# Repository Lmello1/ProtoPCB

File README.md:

# ProtoPCB

Business card PCB and pocket Attiny3227 and LED matrix playground. Powered by a CR2032 battery

## Description

A business card PCB based on the ATTINY3227 chipset. Using 4 74HC595D shift registers to drive a 256 LED matrix. With a standard UDPI interface and 3 input buttons the possibilities are endless.
The current code includes various games and demo programs. Please feel free to make your own and share!

NOTE: Shift register U3 is reversed for easier routing.

## Current programs
* Snake

## Coming soon
* Pong
* Tic Tac Toe
* Tetris

## LED matrix info
```
                 led matrix data flow
attiny3227
V
\_________>_______________________>______________________
         U1                      U2                      \
 ____________________    ____________________             |
/                    \  /                    \            |
X  X  X  X  X  X  X  X  X  X  X  X  X  X  X  X \          |
X  X  X  X  X  X  X  X  X  X  X  X  X  X  X  X |          |
X  X  X  X  X  X  X  X  X  X  X  X  X  X  X  X |          |
X  X  X  X  X  X  X  X  X  X  X  X  X  X  X  X |---- U3---V--(REVERSED)
X  X  X  X  X  X  X  X  X  X  X  X  X  X  X  X |          |
X  X  X  X  X  X  X  X  X  X  X  X  X  X  X  X |          |
X  X  X  X  X  X  X  X  X  X  X  X  X  X  X  X |          |
X  X  X  X  X  X  X  X  X  X  X  X  X  X  X  X /          |
X  X  X  X  X  X  X  X  X  X  X  X  X  X  X  X \          |
X  X  X  X  X  X  X  X  X  X  X  X  X  X  X  X |          |
X  X  X  X  X  X  X  X  X  X  X  X  X  X  X  X |          |
X  X  X  X  X  X  X  X  X  X  X  X  X  X  X  X |---- U4   V
X  X  X  X  X  X  X  X  X  X  X  X  X  X  X  X |          |
X  X  X  X  X  X  X  X  X  X  X  X  X  X  X  X |          |
X  X  X  X  X  X  X  X  X  X  X  X  X  X  X  X |          |
X  X  X  X  X  X  X  X  X  X  X  X  X  X  X  X /          *
```

## PCB Revision History
* Rev 1.0 - 1st working version (Do not recreate-one shorted track) NOTE: Removed from github

* Rev 2.0 - Vertical PCB format and visual improvements. Changed foorptints for shift registers

* Rev 3.0 - CR2032 battery holder added for the back, Track routing improvements

## Creators

Landon Mello
[@Landon_Mello](https://twitter.com/Landon_Mello_)

Ben Liebmann

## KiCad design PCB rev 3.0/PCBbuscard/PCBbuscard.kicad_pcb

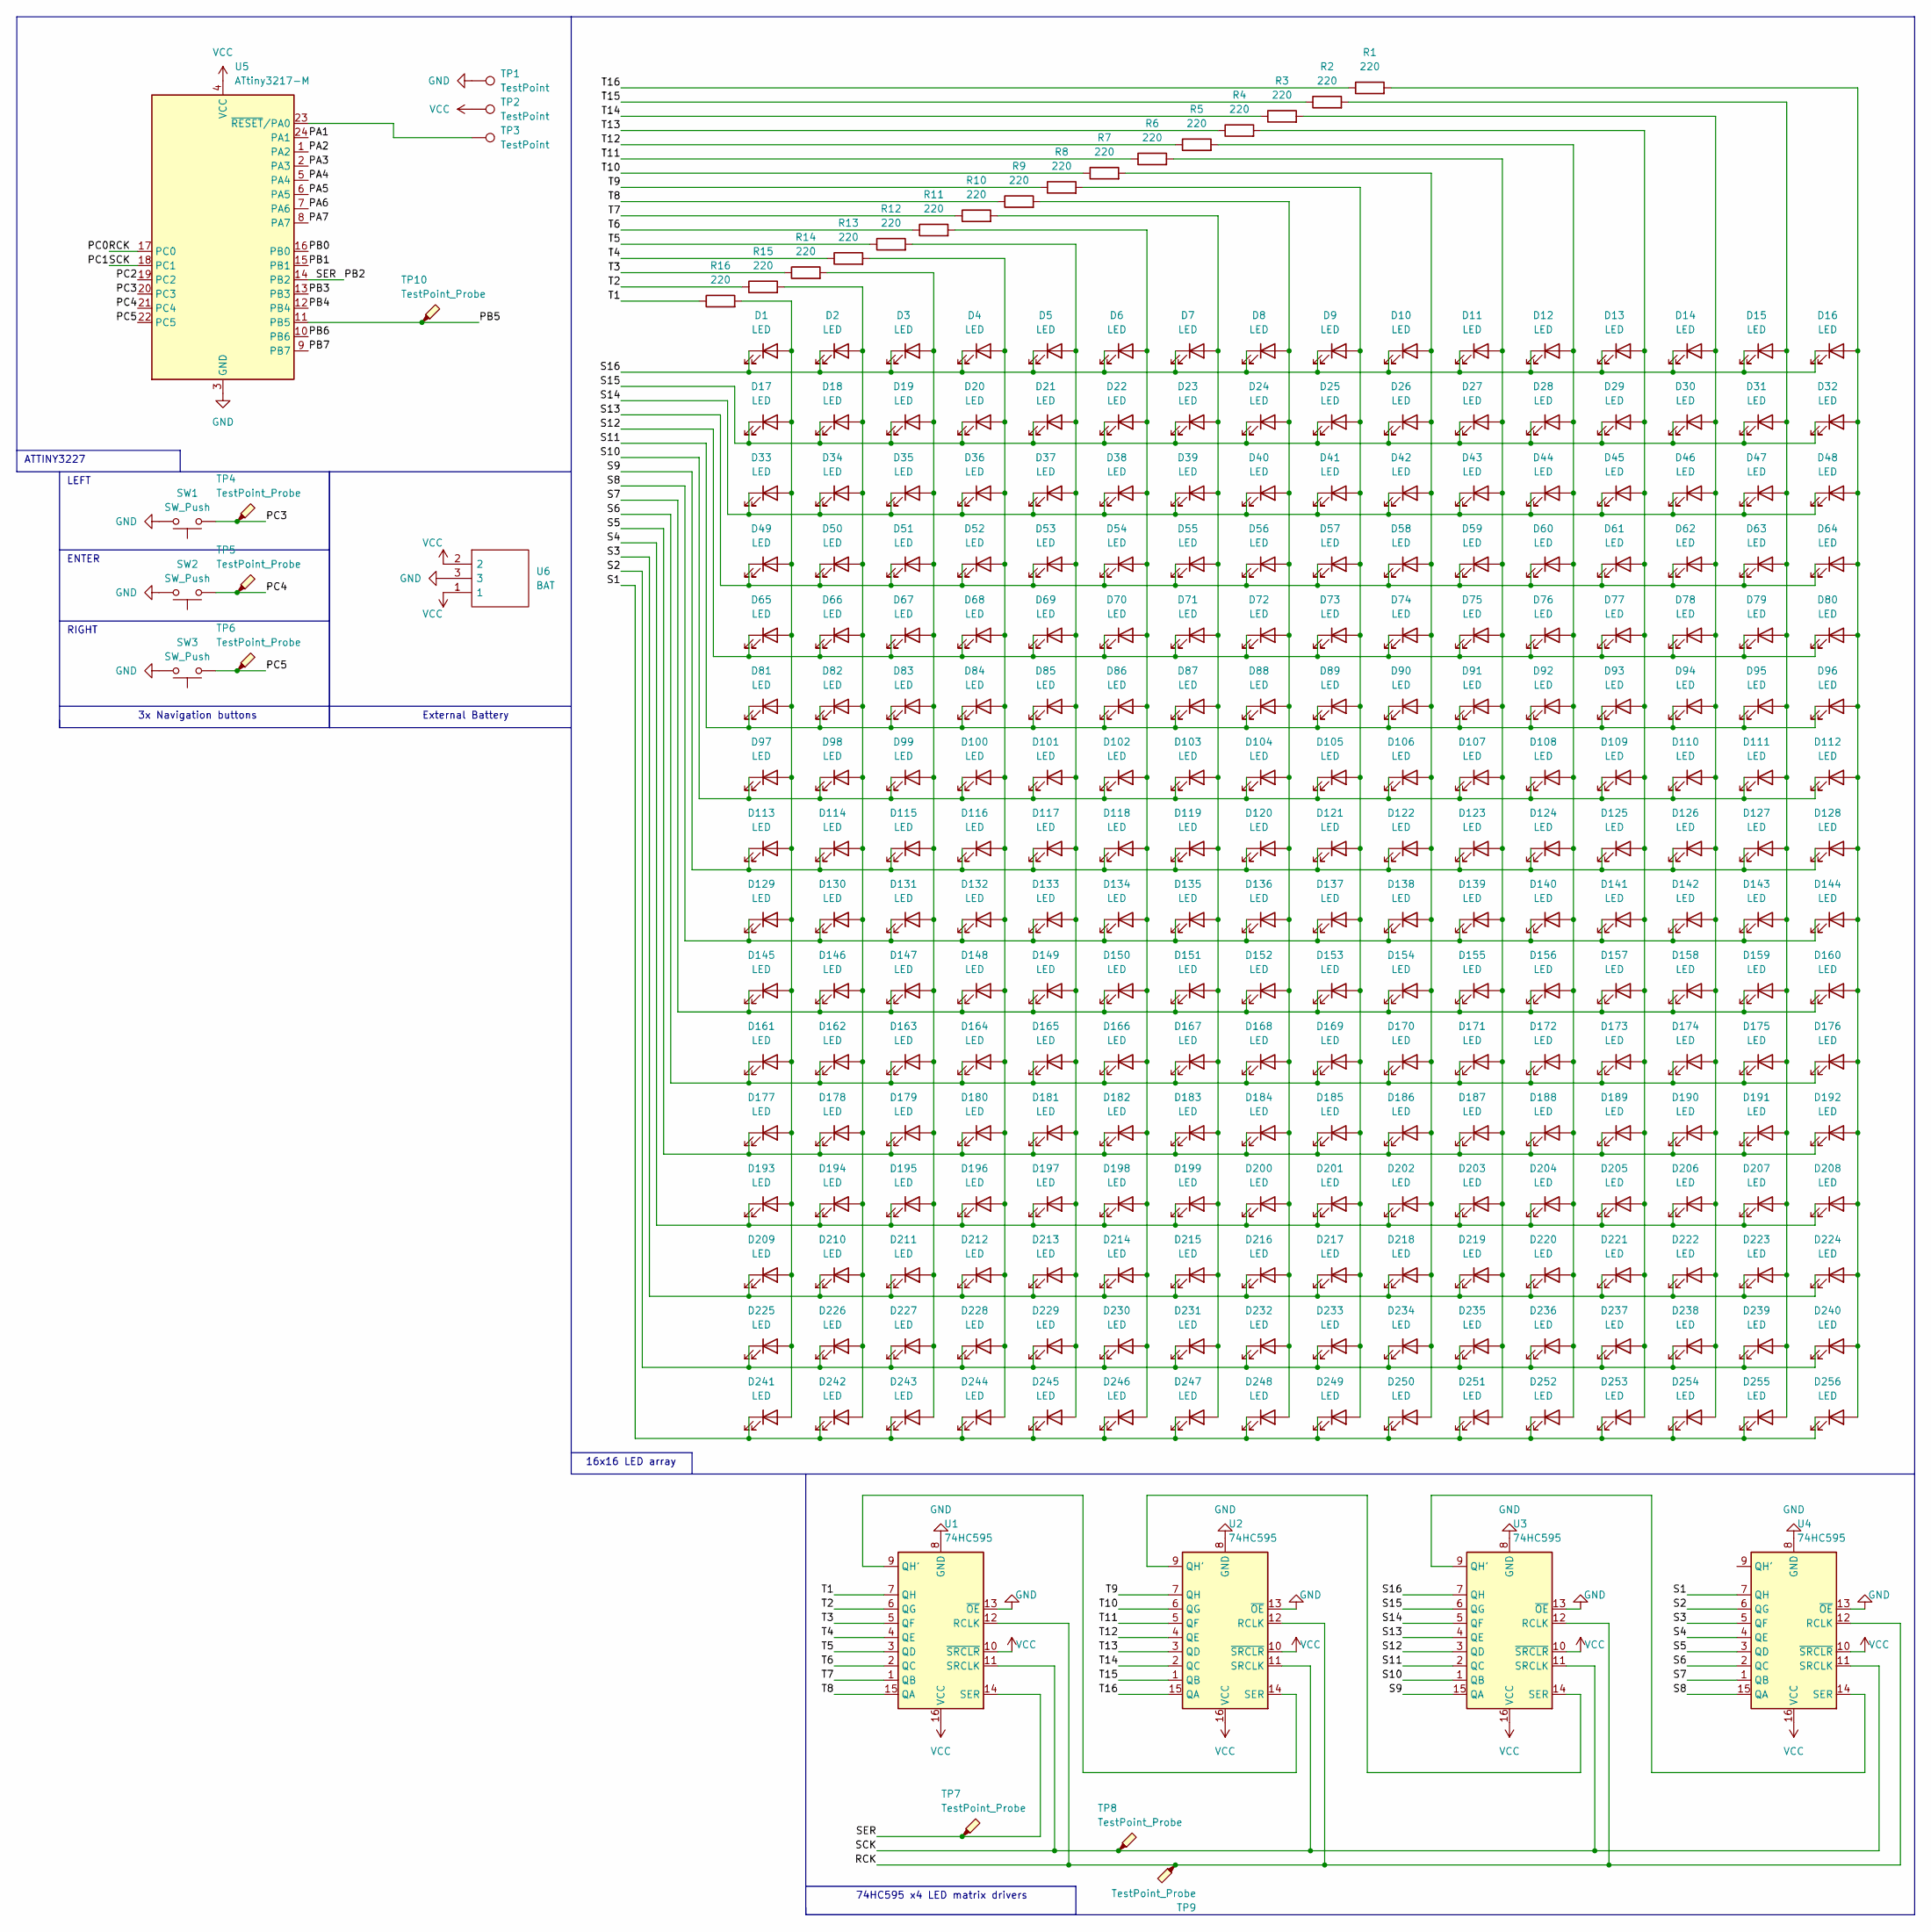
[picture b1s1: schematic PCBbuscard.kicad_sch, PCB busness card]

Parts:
D1, D2, D3, D4, D5, D6, D7, D8, D9, D10, D11, D12, D13, D14, D15, D16, D17, D18, D19, D20, D21, D22, D23, D24, D25, D26, D27, D28, D29, D30, D31, D32, D33, D34, D35, D36, D37, D38, D39, D40, D41, D42, D43, D44, D45, D46, D47, D48, D49, D50, D51, D52, D53, D54, D55, D56, D57, D58, D59, D60, D61, D62, D63, D64, D65, D66, D67, D68, D69, D70, D71, D72, D73, D74, D75, D76, D77, D78, D79, D80, D81, D82, D83, D84, D85, D86, D87, D88, D89, D90, D91, D92, D93, D94, D95, D96, D97, D98, D99, D100, D101, D102, D103, D104, D105, D106, D107, D108, D109, D110, D111, D112, D113, D114, D115, D116, D117, D118, D119, D120, D121, D122, D123, D124, D125, D126, D127, D128, D129, D130, D131, D132, D133, D134, D135, D136, D137, D138, D139, D140, D141, D142, D143, D144, D145, D146, D147, D148, D149, D150, D151, D152, D153, D154, D155, D156, D157, D158, D159, D160, D161, D162, D163, D164, D165, D166, D167, D168, D169, D170, D171, D172, D173, D174, D175, D176, D177, D178, D179, D180, D181, D182, D183, D184, D185, D186, D187, D188, D189, D190, D191, D192, D193, D194, D195, D196, D197, D198, D199, D200, D201, D202, D203, D204, D205, D206, D207, D208, D209, D210, D211, D212, D213, D214, D215, D216, D217, D218, D219, D220, D221, D222, D223, D224, D225, D226, D227, D228, D229, D230, D231, D232, D233, D234, D235, D236, D237, D238, D239, D240, D241, D242, D243, D244, D245, D246, D247, D248, D249, D250, D251, D252, D253, D254, D255, D256: LED; LED_0603_1608Metric_no_text
R1, R2, R3, R4, R5, R6, R7, R8, R9, R10, R11, R12, R13, R14, R15, R16: 220; R_0805_2012Metric_Pad1.20x1.40mm_HandSolder
SW1, SW2, SW3: SW_Push; SW_DIP_SPSTx01_Slide_6.7x4.1mm_W6.73mm_P2.54mm_LowProfile_J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
TP1, TP2, TP3: TestPoint; Pin_D1.1mm_L8.5mm_W2.5mm_FlatFork
TP4, TP5, TP6, TP7, TP8, TP9: TestPoint_Probe; TestPoint_THTPad_1.0x1.0mm_Drill0.5mm
TP10: TestPoint_Probe; Pin_D1.1mm_L8.5mm_W2.5mm_FlatFork
U1, U2, U3, U4: 74HC595; SOIC127P600X175-16N
U5: ATtiny3217-M; QFN-24-1EP_4x4mm_P0.5mm_EP2.6x2.6mm_ThermalVias
U6: BAT; BATHLD001; Mouser Part Number 712-BAT-HLD-001

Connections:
/PA1: U5.24 (PA1)
/PA2: U5.1 (PA2)
/PA3: U5.2 (PA3)
/PA4: U5.5 (PA4)
/PA5: U5.6 (PA5)
/PA6: U5.7 (PA6)
/PA7: U5.8 (PA7)
/PB0: U5.16 (PB0)
/PB1: U5.15 (PB1)
/PB2: TP7.1, U1.14 (SER), U5.14 (PB2)
/PB3: U5.13 (PB3)
/PB4: U5.12 (PB4)
/PB5: TP10.1, U5.11 (PB5); also elsewhere on the board
/PB6: U5.10 (PB6)
/PB7: U5.9 (PB7)
/PC0: TP9.1, U1.12 (RCLK), U2.12 (RCLK), U3.12 (RCLK), U4.12 (RCLK), U5.17 (PC0)
/PC1: TP8.1, U1.11 (SRCLK), U2.11 (SRCLK), U3.11 (SRCLK), U4.11 (SRCLK), U5.18 (PC1)
/PC2: U5.19 (PC2)
/PC3: SW1.1, TP4.1, U5.20 (PC3)
/PC4: SW2.1, TP5.1, U5.21 (PC4)
/PC5: SW3.1, TP6.1, U5.22 (PC5)
/S1: D241.1 (K), D242.1 (K), D243.1 (K), D244.1 (K), D245.1 (K), D246.1 (K), D247.1 (K), D248.1 (K), D249.1 (K), D250.1 (K), D251.1 (K), D252.1 (K), D253.1 (K), D254.1 (K), D255.1 (K), D256.1 (K), U4.7 (QH)
/S2: D225.1 (K), D226.1 (K), D227.1 (K), D228.1 (K), D229.1 (K), D230.1 (K), D231.1 (K), D232.1 (K), D233.1 (K), D234.1 (K), D235.1 (K), D236.1 (K), D237.1 (K), D238.1 (K), D239.1 (K), D240.1 (K), U4.6 (QG)
/S3: D209.1 (K), D210.1 (K), D211.1 (K), D212.1 (K), D213.1 (K), D214.1 (K), D215.1 (K), D216.1 (K), D217.1 (K), D218.1 (K), D219.1 (K), D220.1 (K), D221.1 (K), D222.1 (K), D223.1 (K), D224.1 (K), U4.5 (QF)
/S4: D193.1 (K), D194.1 (K), D195.1 (K), D196.1 (K), D197.1 (K), D198.1 (K), D199.1 (K), D200.1 (K), D201.1 (K), D202.1 (K), D203.1 (K), D204.1 (K), D205.1 (K), D206.1 (K), D207.1 (K), D208.1 (K), U4.4 (QE)
/S5: D177.1 (K), D178.1 (K), D179.1 (K), D180.1 (K), D181.1 (K), D182.1 (K), D183.1 (K), D184.1 (K), D185.1 (K), D186.1 (K), D187.1 (K), D188.1 (K), D189.1 (K), D190.1 (K), D191.1 (K), D192.1 (K), U4.3 (QD)
/S6: D161.1 (K), D162.1 (K), D163.1 (K), D164.1 (K), D165.1 (K), D166.1 (K), D167.1 (K), D168.1 (K), D169.1 (K), D170.1 (K), D171.1 (K), D172.1 (K), D173.1 (K), D174.1 (K), D175.1 (K), D176.1 (K), U4.2 (QC)
/S7: D145.1 (K), D146.1 (K), D147.1 (K), D148.1 (K), D149.1 (K), D150.1 (K), D151.1 (K), D152.1 (K), D153.1 (K), D154.1 (K), D155.1 (K), D156.1 (K), D157.1 (K), D158.1 (K), D159.1 (K), D160.1 (K), U4.1 (QB)
/S8: D129.1 (K), D130.1 (K), D131.1 (K), D132.1 (K), D133.1 (K), D134.1 (K), D135.1 (K), D136.1 (K), D137.1 (K), D138.1 (K), D139.1 (K), D140.1 (K), D141.1 (K), D142.1 (K), D143.1 (K), D144.1 (K), U4.15 (QA)
/S9: D113.1 (K), D114.1 (K), D115.1 (K), D116.1 (K), D117.1 (K), D118.1 (K), D119.1 (K), D120.1 (K), D121.1 (K), D122.1 (K), D123.1 (K), D124.1 (K), D125.1 (K), D126.1 (K), D127.1 (K), D128.1 (K), U3.15 (QA)
/S10: D97.1 (K), D98.1 (K), D99.1 (K), D100.1 (K), D101.1 (K), D102.1 (K), D103.1 (K), D104.1 (K), D105.1 (K), D106.1 (K), D107.1 (K), D108.1 (K), D109.1 (K), D110.1 (K), D111.1 (K), D112.1 (K), U3.1 (QB)
/S11: D81.1 (K), D82.1 (K), D83.1 (K), D84.1 (K), D85.1 (K), D86.1 (K), D87.1 (K), D88.1 (K), D89.1 (K), D90.1 (K), D91.1 (K), D92.1 (K), D93.1 (K), D94.1 (K), D95.1 (K), D96.1 (K), U3.2 (QC)
/S12: D65.1 (K), D66.1 (K), D67.1 (K), D68.1 (K), D69.1 (K), D70.1 (K), D71.1 (K), D72.1 (K), D73.1 (K), D74.1 (K), D75.1 (K), D76.1 (K), D77.1 (K), D78.1 (K), D79.1 (K), D80.1 (K), U3.3 (QD)
/S13: D49.1 (K), D50.1 (K), D51.1 (K), D52.1 (K), D53.1 (K), D54.1 (K), D55.1 (K), D56.1 (K), D57.1 (K), D58.1 (K), D59.1 (K), D60.1 (K), D61.1 (K), D62.1 (K), D63.1 (K), D64.1 (K), U3.4 (QE)
/S14: D33.1 (K), D34.1 (K), D35.1 (K), D36.1 (K), D37.1 (K), D38.1 (K), D39.1 (K), D40.1 (K), D41.1 (K), D42.1 (K), D43.1 (K), D44.1 (K), D45.1 (K), D46.1 (K), D47.1 (K), D48.1 (K), U3.5 (QF)
/S15: D17.1 (K), D18.1 (K), D19.1 (K), D20.1 (K), D21.1 (K), D22.1 (K), D23.1 (K), D24.1 (K), D25.1 (K), D26.1 (K), D27.1 (K), D28.1 (K), D29.1 (K), D30.1 (K), D31.1 (K), D32.1 (K), U3.6 (QG)
/S16: D1.1 (K), D2.1 (K), D3.1 (K), D4.1 (K), D5.1 (K), D6.1 (K), D7.1 (K), D8.1 (K), D9.1 (K), D10.1 (K), D11.1 (K), D12.1 (K), D13.1 (K), D14.1 (K), D15.1 (K), D16.1 (K), U3.7 (QH)
/T1: R16.1, U1.7 (QH)
/T2: R15.1, U1.6 (QG)
/T3: R14.1, U1.5 (QF)
/T4: R13.1, U1.4 (QE)
/T5: R12.1, U1.3 (QD)
/T6: R11.1, U1.2 (QC)
/T7: R10.1, U1.1 (QB)
/T8: R9.1, U1.15 (QA)
/T9: R8.1, U2.7 (QH)
/T10: R7.1, U2.6 (QG)
/T11: R6.1, U2.5 (QF)
/T12: R5.1, U2.4 (QE)
/T13: R4.1, U2.3 (QD)
/T14: R3.1, U2.2 (QC)
/T15: R2.1, U2.1 (QB)
/T16: R1.1, U2.15 (QA)
GND: SW1.2, SW2.2, SW3.2, TP1.1, U1.8 (GND), U1.13 (~OE), U2.8 (GND), U2.13 (~OE), U3.8 (GND), U3.13 (~OE), U4.8 (GND), U4.13 (~OE), U5.3 (GND), U5.25 (GND), U6.3; also elsewhere on the board
unnamed: D1.2 (A), D17.2 (A), D33.2 (A), D49.2 (A), D65.2 (A), D81.2 (A), D97.2 (A), D113.2 (A), D129.2 (A), D145.2 (A), D161.2 (A), D177.2 (A), D193.2 (A), D209.2 (A), D225.2 (A), D241.2 (A), R16.2
unnamed: D10.2 (A), D26.2 (A), D42.2 (A), D58.2 (A), D74.2 (A), D90.2 (A), D106.2 (A), D122.2 (A), D138.2 (A), D154.2 (A), D170.2 (A), D186.2 (A), D202.2 (A), D218.2 (A), D234.2 (A), D250.2 (A), R7.2
unnamed: D4.2 (A), D20.2 (A), D36.2 (A), D52.2 (A), D68.2 (A), D84.2 (A), D100.2 (A), D116.2 (A), D132.2 (A), D148.2 (A), D164.2 (A), D180.2 (A), D196.2 (A), D212.2 (A), D228.2 (A), D244.2 (A), R13.2
unnamed: D5.2 (A), D21.2 (A), D37.2 (A), D53.2 (A), D69.2 (A), D85.2 (A), D101.2 (A), D117.2 (A), D133.2 (A), D149.2 (A), D165.2 (A), D181.2 (A), D197.2 (A), D213.2 (A), D229.2 (A), D245.2 (A), R12.2
unnamed: D6.2 (A), D22.2 (A), D38.2 (A), D54.2 (A), D70.2 (A), D86.2 (A), D102.2 (A), D118.2 (A), D134.2 (A), D150.2 (A), D166.2 (A), D182.2 (A), D198.2 (A), D214.2 (A), D230.2 (A), D246.2 (A), R11.2
unnamed: D7.2 (A), D23.2 (A), D39.2 (A), D55.2 (A), D71.2 (A), D87.2 (A), D103.2 (A), D119.2 (A), D135.2 (A), D151.2 (A), D167.2 (A), D183.2 (A), D199.2 (A), D215.2 (A), D231.2 (A), D247.2 (A), R10.2
unnamed: D8.2 (A), D24.2 (A), D40.2 (A), D56.2 (A), D72.2 (A), D88.2 (A), D104.2 (A), D120.2 (A), D136.2 (A), D152.2 (A), D168.2 (A), D184.2 (A), D200.2 (A), D216.2 (A), D232.2 (A), D248.2 (A), R9.2
unnamed: D9.2 (A), D25.2 (A), D41.2 (A), D57.2 (A), D73.2 (A), D89.2 (A), D105.2 (A), D121.2 (A), D137.2 (A), D153.2 (A), D169.2 (A), D185.2 (A), D201.2 (A), D217.2 (A), D233.2 (A), D249.2 (A), R8.2
unnamed: D11.2 (A), D27.2 (A), D43.2 (A), D59.2 (A), D75.2 (A), D91.2 (A), D107.2 (A), D123.2 (A), D139.2 (A), D155.2 (A), D171.2 (A), D187.2 (A), D203.2 (A), D219.2 (A), D235.2 (A), D251.2 (A), R6.2
unnamed: D12.2 (A), D28.2 (A), D44.2 (A), D60.2 (A), D76.2 (A), D92.2 (A), D108.2 (A), D124.2 (A), D140.2 (A), D156.2 (A), D172.2 (A), D188.2 (A), D204.2 (A), D220.2 (A), D236.2 (A), D252.2 (A), R5.2
unnamed: D13.2 (A), D29.2 (A), D45.2 (A), D61.2 (A), D77.2 (A), D93.2 (A), D109.2 (A), D125.2 (A), D141.2 (A), D157.2 (A), D173.2 (A), D189.2 (A), D205.2 (A), D221.2 (A), D237.2 (A), D253.2 (A), R4.2
unnamed: D14.2 (A), D30.2 (A), D46.2 (A), D62.2 (A), D78.2 (A), D94.2 (A), D110.2 (A), D126.2 (A), D142.2 (A), D158.2 (A), D174.2 (A), D190.2 (A), D206.2 (A), D222.2 (A), D238.2 (A), D254.2 (A), R3.2
unnamed: D15.2 (A), D31.2 (A), D47.2 (A), D63.2 (A), D79.2 (A), D95.2 (A), D111.2 (A), D127.2 (A), D143.2 (A), D159.2 (A), D175.2 (A), D191.2 (A), D207.2 (A), D223.2 (A), D239.2 (A), D255.2 (A), R2.2
unnamed: D16.2 (A), D32.2 (A), D48.2 (A), D64.2 (A), D80.2 (A), D96.2 (A), D112.2 (A), D128.2 (A), D144.2 (A), D160.2 (A), D176.2 (A), D192.2 (A), D208.2 (A), D224.2 (A), D240.2 (A), D256.2 (A), R1.2
unnamed: D2.2 (A), D18.2 (A), D34.2 (A), D50.2 (A), D66.2 (A), D82.2 (A), D98.2 (A), D114.2 (A), D130.2 (A), D146.2 (A), D162.2 (A), D178.2 (A), D194.2 (A), D210.2 (A), D226.2 (A), D242.2 (A), R15.2
unnamed: D3.2 (A), D19.2 (A), D35.2 (A), D51.2 (A), D67.2 (A), D83.2 (A), D99.2 (A), D115.2 (A), D131.2 (A), D147.2 (A), D163.2 (A), D179.2 (A), D195.2 (A), D211.2 (A), D227.2 (A), D243.2 (A), R14.2
unnamed 70: TP3.1, U5.23 (~RESET/PA0); also elsewhere on the board
unnamed: U1.9 (QH'), U2.14 (SER)
unnamed: U2.9 (QH'), U3.14 (SER)
unnamed: U3.9 (QH'), U4.14 (SER)
VCC: TP2.1, U1.10 (~SRCLR), U1.16 (VCC), U2.10 (~SRCLR), U2.16 (VCC), U3.10 (~SRCLR), U3.16 (VCC), U4.10 (~SRCLR), U4.16 (VCC), U5.4 (VCC), U6.1, U6.2; also elsewhere on the board

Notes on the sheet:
External Battery
ENTER
RIGHT
3x Navigation buttons
74HC595 x4 LED matrix drivers
16x16 LED array
LEFT
ATTINY3227

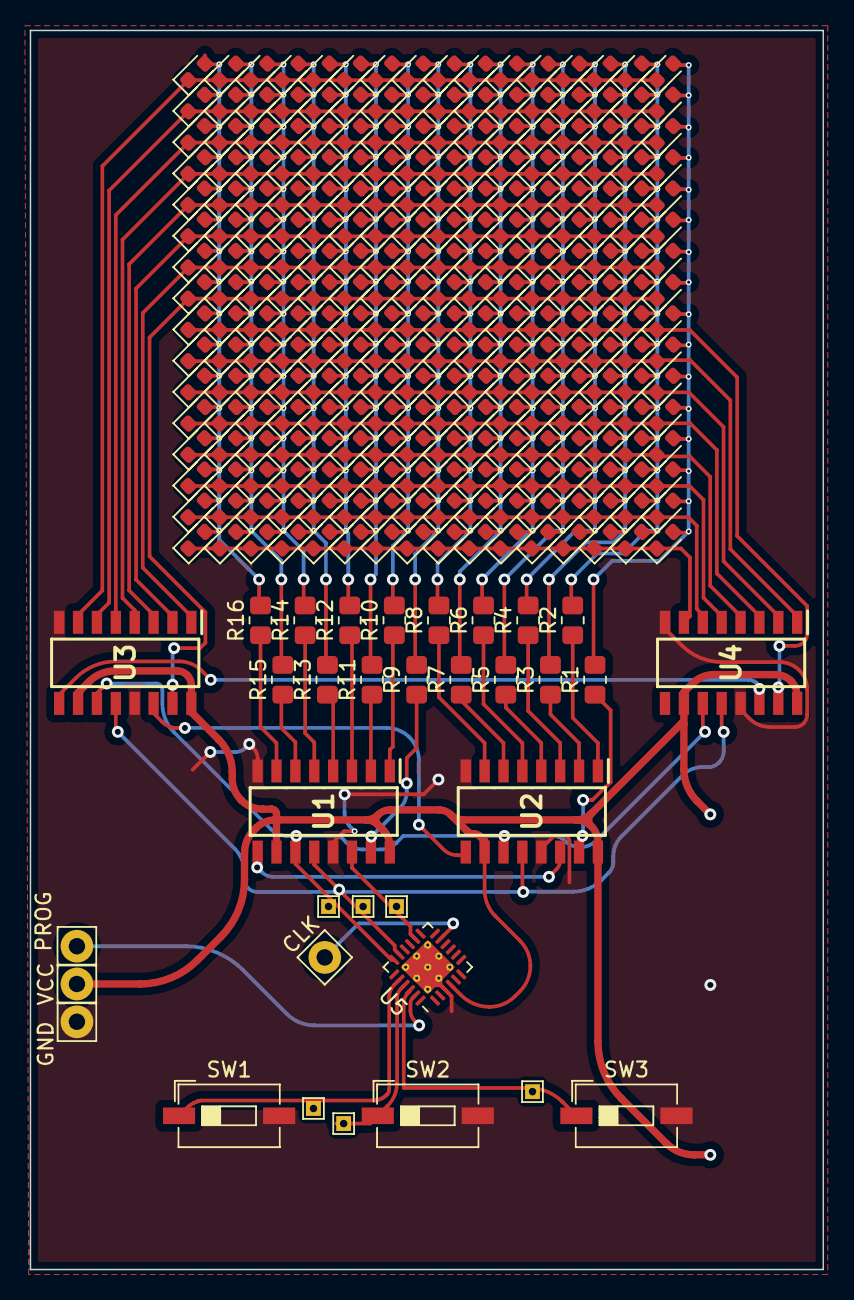
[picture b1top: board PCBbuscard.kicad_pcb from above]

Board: 2 copper layers, 53.3 x 83.3 mm, 291 parts (1 on the bottom side), 61 nets.

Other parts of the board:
CLK: TestPoint_Probe; Pin_D1.1mm_L8.5mm_W2.5mm_FlatFork
GND: TestPoint; Pin_D1.1mm_L8.5mm_W2.5mm_FlatFork
PROG: TestPoint; Pin_D1.1mm_L8.5mm_W2.5mm_FlatFork
VCC: TestPoint; Pin_D1.1mm_L8.5mm_W2.5mm_FlatFork

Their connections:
/PB5: CLK.1; also elsewhere on the board
GND: GND.1; also elsewhere on the board
unnamed 70: PROG.1; also elsewhere on the board
VCC: VCC.1; also elsewhere on the board

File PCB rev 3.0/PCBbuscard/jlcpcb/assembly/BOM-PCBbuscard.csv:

Comment,Designator,Footprint,LCSC
220,"R1,R10,R11,R12,R13,R14,R15,R16,R2,R3,R4,R5,R6,R7,R8,R9",R_0805_2012Metric_Pad1.20x1.40mm_HandSolder,C17557
LED,"D1,D10,D100,D101,D102,D103,D104,D105,D106,D107,D108,D109,D11,D110,D111,D112,D113,D114,D115,D116,D117,D118,D119,D12,D120,D121,D122,D123,D124,D125,D126,D127,D128,D129,D13,D130,D131,D132,D133,D134,D135,D136,D137,D138,D139,D14,D140,D141,D142,D143,D144,D145,D146,D147,D148,D149,D15,D150,D151,D152,D153,D154,D155,D156,D157,D158,D159,D16,D160,D161,D162,D163,D164,D165,D166,D167,D168,D169,D17,D170,D171,D172,D173,D174,D175,D176,D177,D178,D179,D18,D180,D181,D182,D183,D184,D185,D186,D187,D188,D189,D19,D190,D191,D192,D193,D194,D195,D196,D197,D198,D199,D2,D20,D200,D201,D202,D203,D204,D205,D206,D207,D208,D209,D21,D210,D211,D212,D213,D214,D215,D216,D217,D218,D219,D22,D220,D221,D222,D223,D224,D225,D226,D227,D228,D229,D23,D230,D231,D232,D233,D234,D235,D236,D237,D238,D239,D24,D240,D241,D242,D243,D244,D245,D246,D247,D248,D249,D25,D250,D251,D252,D253,D254,D255,D256,D26,D27,D28,D29,D3,D30,D31,D32,D33,D34,D35,D36,D37,D38,D39,D4,D40,D41,D42,D43,D44,D45,D46,D47,D48,D49,D5,D50,D51,D52,D53,D54,D55,D56,D57,D58,D59,D6,D60,D61,D62,D63,D64,D65,D66,D67,D68,D69,D7,D70,D71,D72,D73,D74,D75,D76,D77,D78,D79,D8,D80,D81,D82,D83,D84,D85,D86,D87,D88,D89,D9,D90,D91,D92,D93,D94,D95,D96,D97,D98,D99",LED_0603_1608Metric_no_text,C2290
SW_Push,"SW1,SW2,SW3",SW_DIP_SPSTx01_Slide_6.7x4.1mm_W6.73mm_P2.54mm_LowProfile_JPin,C354942
74HC595,U4,SOIC127P600X175-16N,
74HC595,U1,SOIC127P600X175-16N,
74HC595,U3,SOIC127P600X175-16N,
74HC595,U2,SOIC127P600X175-16N,
ATtiny3217-M,U5,QFN-24-1EP_4x4mm_P0.5mm_EP2.6x2.6mm_ThermalVias,
TestPoint_Probe,TP9,TestPoint_THTPad_1.0x1.0mm_Drill0.5mm,
TestPoint_Probe,TP8,TestPoint_THTPad_1.0x1.0mm_Drill0.5mm,
TestPoint_Probe,TP7,TestPoint_THTPad_1.0x1.0mm_Drill0.5mm,
TestPoint_Probe,TP6,TestPoint_THTPad_1.0x1.0mm_Drill0.5mm,
TestPoint_Probe,TP5,TestPoint_THTPad_1.0x1.0mm_Drill0.5mm,
TestPoint_Probe,TP4,TestPoint_THTPad_1.0x1.0mm_Drill0.5mm,
BAT,U6,BATHLD001,

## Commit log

2022-07-17 Added IMG folder and supporting files
2022-07-23 Added test matrix file
2022-07-23 pushing files
2022-07-23 Edits to matrix test program for 74HC595 testing
2022-07-26 Update formatting + convert constants to constexprs
    -- Identifiers for pin constants converted to SCREAMING_SNAKE_CASE per most C/C++ standard practice
    -- Pin constants converted from `const int`s to `constexpr uint8_t`s more strictly adheres to how modern C++ should define a constant value
2022-07-26 Added timer1 hardware interrupt for asynchronous LED matrix updates
    -- Enabled interrupt on timer1 that displays the value of the current row on the LED matrix
    -- The processor will now constantly update the LED matrix
    -- Note that any mutations to the `matrix_buf` global MUST be in an ATOMIC_BLOCK or with NoIterrupts called, or else the interrupt may be triggered while writing data to the buffer, causing scrambled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
    to appear on the LED matrix
2022-07-26 Updated refresh rate of the LED matrix to be 30hz
2022-07-26 Added testing pattern for the LED matrix
2022-07-27 PCB rev 1.0! (do not use/under heavy development)
2022-07-27 Corrected timer and display code
2022-07-27 Updated matrix refresh rate to 15hz
2022-07-27 Actually Updated matrix refresh rate to 15hz (prev. commit was 150hz)
2022-07-27 Update screen buffer to support atomic + more efficient operations
    - `rowmask_t` converted to `uint8_t` and `screen_buf` now contains 32 elements, 2 for each row
    - uint8_t operations are atomic on the 8-bit attiny3227, so can be safely executed without the need for an ATOMIC_BLOCK
    - 8 bit elements can be modified in 3 instructions (load + modify + store), saving instructions compared to 16 bit elements, which had unneeded instructions for loading two 8-bit values
    - GCC attributes added to functions forcing inlining, from compiler explorer output each call to the `set` and `unset` functions should now take 3 instructions
    - Split matrix code into a separate file to aid readability
    - Renam
2022-07-27 Fixed LED matrix display
    - Fixes LED matrix display control
2022-07-27 Fix lower right quadrant display bug, add moving test pattern
2022-07-27 Update contributors
2022-07-28 Updated design
2022-08-10 Changed timer used for screen rendering interrupts to timer A and update refresh rate
    - Timer A used instead of timer B to use the 1024 clock prescaler only available on timer A
    - Refresh rate changed to 15hz
2022-08-14 Test program
2022-08-14 Reverted test program
2022-08-14 Attempted fix for new shift register layout
2022-08-22 Updated matrix control
2022-08-23 Fixed ILLEGAL_MCU_STATE: Running error by updating interrupt source for draw procedure
2022-08-23 Reordered Y axis of LED matrix and partially re-wrote interrupt in assembly
    - LED matrix coordinates now more closely represent standard graph coordinates, e.g. y = 0 is the bottom of the screen, while y = 15 is the top of the screen
    - Rewrite of column bit banging portion of screen rendering interrupt in assembly
    - Rewrite in asm favors speed over size, minimizing branching and cpu cycles at the expense of ~50 bytes of program memory
    - For half the screen, column bits are pushed at the fastest the cpu can possibly switch an IO pin without hardware PWM; i.e. around 8Mhz
2022-08-23 Updated assembly comments, replaced uneeded compare instruction - Assembly comments added + edited existing comments to more accurately reflect what is being achieved - Removed unneeded instruction c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
2022-08-23 Fixed matrix regression caused by ca9f1d100d7394185e08490f4857f75320bd97b1 by replacing brbs instruction checking for carry with brbs instruction checking for negative (underflow) flags
2022-08-23 Removed uneeded breq instruction, replaced with comparison of higher number
2022-08-23 Fixed data race in LED matrix buffer by changing millis() source to RTC
2022-08-24 Fully rewrote rendering interrupt handler in assembly
    - Full rewrite in assembly favors speed over size, with manually unrolled loops, etc.
2022-08-27 Implemented snake
2022-08-29 Update README.md
    Added more info and Coming Soon list to the readme
2022-08-29 PCB rev 2.0 update
2022-08-30 BOM + PCB photos
2022-09-01 fixed rev #
